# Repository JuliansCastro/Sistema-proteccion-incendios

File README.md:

# Sistema de Protección contra Incendios con LoRa y Raspberry Pi Pico

## Resumen

Este proyecto desarrolla un sistema integral de monitoreo y protección contra incendios forestales utilizando tecnología IoT. El sistema emplea sensores distribuidos que se comunican mediante protocolo LoRa para detectar condiciones ambientales críticas (temperatura, humedad y presencia de llamas) y transmitir los datos a una estación central basada en Raspberry Pi Pico W que proporciona interfaz web para visualización en tiempo real.

## Características Principales

- **Monitoreo Distribuido**: Red de sensores inalámbricos con comunicación LoRa de largo alcance
- **Detección Multiparamétrica**: Sensores de temperatura (DHT11), humedad relativa y detector PIR para llamas
- **Comunicación Robusta**: Protocolo LoRa a 433MHz con alcance de varios kilómetros
- **Interfaz Web**: Servidor HTTP integrado en Raspberry Pi Pico W para visualización remota
- **Display Local**: Pantalla LCD I2C para monitoreo local de datos
- **Alertas en Tiempo Real**: Detección automática de condiciones de riesgo de incendio
- **Arquitectura Modular**: Diseño escalable para múltiples nodos sensores
- **Bajo Consumo**: Optimizado para aplicaciones de campo con alimentación autónoma

## Arquitectura del Sistema

```text
┌─────────────────┐       LoRa 433MHz      ┌──────────────────────┐
│   Nodo Sensor   │ ◄────────────────────► │  Estación Central    │
│  (Tx - Pico)    │                        │  (Rx - Pico W)       │
├─────────────────┤                        ├──────────────────────┤
│ • DHT11         │                        │ • LoRa Receptor      │
│ • PIR Sensor    │                        │ • WiFi Server        │
│ • LoRa Tx       │                        │ • LCD Display        │
│ • Raspberry     │                        │ • Raspberry Pi       │
│   Pi Pico       │                        │   Pico W             │
└─────────────────┘                        └──────────────────────┘
                                                      │
                                                      │ WiFi
                                                      ▼
                                           ┌──────────────────────┐
                                           │   Cliente Web        │
                                           │ (Navegador/App)      │
                                           └──────────────────────┘
```

### Componentes del Sistema

1. **Nodo Transmisor (Tx)**:
   - Raspberry Pi Pico como microcontrolador principal
   - Sensor DHT11 para temperatura y humedad
   - Sensor PIR para detección de movimiento/llamas
   - Módulo LoRa para transmisión de datos
   - Encapsulado 3D impreso para protección ambiental

2. **Estación Receptora (Rx)**:
   - Raspberry Pi Pico W con conectividad WiFi
   - Módulo LoRa para recepción de datos
   - Display LCD I2C 16x2 para visualización local
   - Servidor web HTTP integrado
   - Procesamiento y almacenamiento temporal de datos

3. **Protocolo de Comunicación**:
   - LoRa a 433MHz para comunicación de largo alcance
   - Estructura de paquetes con ID de nodo, datos de sensores y verificación
   - Interfaz web HTTP para acceso remoto

## Tecnologías Utilizadas

### Hardware

- **Microcontroladores**:
  - Raspberry Pi Pico (RP2040)
  - Raspberry Pi Pico W (RP2040 + WiFi)
- **Sensores**:
  - DHT11 (Temperatura y Humedad)
  - PIR Sensor (Detección de movimiento/llamas)
- **Comunicación**:
  - Módulos LoRa SX1276/SX1278 (433MHz)
  - WiFi integrado (Pico W)
- **Display**: LCD I2C 16x2 con controlador PCF8574
- **PCB**: Diseño personalizado en KiCad
- **Encapsulado**: Carcasas 3D impresas en PLA/PETG

### Software

- **Lenguajes**: C++ (Arduino Framework)
- **Librerías**:
  - `LoRa.h` - Comunicación LoRa
  - `DHT.h` - Sensor de temperatura/humedad
  - `WiFi.h` - Conectividad inalámbrica
  - `LiquidCrystal_I2C.h` - Control de display
  - `TimeLib.h` - Manejo de tiempo
- **Protocolos**: HTTP, LoRa, I2C, SPI
- **IDE**: Arduino IDE con soporte para RP2040
- **Herramientas de Diseño**:
  - KiCad (Diseño de PCB)
  - Fusion 360 (Modelado 3D)

## Instalación y Configuración

### Requisitos de Hardware

- 2x Raspberry Pi Pico (1x estándar, 1x Pico W)
- 2x Módulos LoRa SX1276/SX1278
- 1x Sensor DHT11
- 1x Sensor PIR
- 1x Display LCD I2C 16x2
- Componentes electrónicos (resistencias, capacitores, conectores)
- PCBs personalizadas o protoboard
- Carcasas 3D impresas
- Fuentes de alimentación (baterías o adaptadores)

### Montaje y Conexiones

#### Nodo Transmisor (Pico)

```text
DHT11:
- VCC → 3.3V
- GND → GND  
- DATA → GPIO 28

PIR Sensor:
- VCC → 5V
- GND → GND
- OUT → GPIO 27

LoRa Module:
- VCC → 3.3V
- GND → GND
- NSS → GPIO 8
- RST → GPIO 9
- DIO0 → GPIO 7
- SCK → GPIO 18
- MISO → GPIO 16
- MOSI → GPIO 19
```

#### Estación Receptora (Pico W)

```text
LoRa Module:
- (Mismas conexiones que Tx)

LCD I2C:
- VCC → 3.3V
- GND → GND
- SDA → GPIO 0
- SCL → GPIO 1
```

### Instalación del Entorno de Software

1. **Configurar Arduino IDE**:

```bash
# Instalar Arduino IDE desde: https://www.arduino.cc/en/software

# Agregar soporte para RP2040:
# File → Preferences → Additional Board Manager URLs
# Agregar: https://github.com/earlephilhower/arduino-pico/releases/download/global/package_rp2040_index.json

# Tools → Board → Boards Manager
# Buscar "pico" e instalar "Raspberry Pi Pico/RP2040"
```

2. **Instalar Librerías Requeridas**:

```bash
# En Arduino IDE: Tools → Manage Libraries
# Instalar:
- DHT sensor library by Adafruit
- LoRa by Sandeep Mistry  
- LiquidCrystal I2C by Frank de Brabander
- Time by Michael Margolis
```

3. **Configurar Red WiFi**:

```cpp
// Editar en RPi_Pico_W_Lora_Rx.ino:
#define SSID "TU_RED_WIFI"
#define PASSWORD "TU_CONTRASEÑA"
```

4. **Cargar Firmware**:

```bash
# 1. Conectar Raspberry Pi Pico manteniendo presionado BOOTSEL
# 2. Seleccionar Board: "Raspberry Pi Pico" o "Raspberry Pi Pico W"
# 3. Cargar RPi_Pico_Lora_Tx.ino en el nodo transmisor
# 4. Cargar RPi_Pico_W_Lora_Rx.ino en la estación receptora
```

## Despliegue

### Ejecución Local

1. **Inicializar Sistema**:
   - Encender nodo transmisor (comenzará a enviar datos cada 20 segundos)
   - Encender estación receptora
   - Verificar conexión LoRa en monitor serial
   - Confirmar conexión WiFi y obtener IP local

2. **Acceso a Interface Web**:
   - Conectarse a la misma red WiFi que el Pico W
   - Abrir navegador en `http://[IP_DEL_PICO_W]`
   - La página se actualiza automáticamente cada 5 segundos

3. **Monitoreo Local**:
   - Visualizar datos en tiempo real en LCD
   - Revisar logs en monitor serial (115200 baud)

### Despliegue en Campo

1. **Preparación**:
   - Instalar nodos en ubicaciones estratégicas
   - Configurar alimentación autónoma (paneles solares/baterías)
   - Verificar cobertura LoRa entre nodos

2. **Red WiFi de Campo**:
   - Configurar hotspot móvil o router portable
   - Ajustar configuración WiFi en código según disponibilidad

## Casos de Uso

### Monitoreo Forestal

```text
Escenario: Bosque de 10 km²
- 5 nodos transmisores distribuidos estratégicamente
- 1 estación central con conectividad satelital/celular
- Alertas automáticas cuando temperatura > 35°C y humedad < 30%
- Detección temprana de focos de incendio mediante sensores PIR
```

### Instalaciones Industriales

```text
Escenario: Almacén de materiales inflamables
- Nodos en cada sector crítico
- Integración con sistemas de extinción automática
- Dashboard web para personal de seguridad
- Registro histórico de condiciones ambientales
```

### Agricultura de Precisión

```text
Escenario: Invernaderos automatizados
- Monitoreo continuo de microclima
- Optimización de sistemas de riego
- Prevención de condiciones de estrés térmico
- Alertas de condiciones anómalas
```

## Estructura del Proyecto

```text
Sistema-proteccion-incendios/
├── README.md
├── Carcasa - Fusion360/           # Modelos 3D de encapsulados
│   ├── 3D/                        # Archivos STL para impresión
│   └── Fusion360/                 # Archivos fuente F3D
├── Diseño electrónico - PCB KiCad/ # Diseños de circuitos impresos
│   ├── sys_incendios_rx/          # PCB para receptor
│   ├── sys_incendios_Tx/          # PCB para transmisor
│   └── Fab_PCB_diseno/            # Archivos Gerber para fabricación
├── Software microcontroladores/    # Código fuente
│   ├── RPi_Pico_Lora_Tx/         # Firmware nodo transmisor
│   └── RPi_Pico_W_Lora_Rx/       # Firmware estación receptora
├── Docs/                          # Documentación técnica
│   ├── BOOM Materials.xlsx        # Lista de materiales
│   └── Datasheets/                # Hojas de datos de componentes
└── imgs/                          # Imágenes del proyecto
```

## Desarrollo Futuro

- [ ] Integración con bases de datos (SQLite/MySQL)
- [ ] API REST para integración con terceros
- [ ] Aplicación móvil nativa
- [ ] Protocolo MQTT para IoT
- [ ] Integración con servicios en la nube (AWS IoT, Azure IoT)
- [ ] Algoritmos de machine learning para predicción
- [ ] Soporte para más tipos de sensores
- [ ] Mesh networking con múltiples receptores

## Contribuciones

Las contribuciones son bienvenidas. Para cambios importantes:

1. Fork el proyecto
2. Crear una rama para tu feature (`git checkout -b feature/AmazingFeature`)
3. Commit tus cambios (`git commit -m 'Add some AmazingFeature'`)
4. Push a la rama (`git push origin feature/AmazingFeature`)
5. Abrir un Pull Request

## Licencia

Este proyecto está licenciado bajo la Licencia MIT - ver el archivo [LICENSE](LICENSE) para detalles.

## Créditos y Autores

**Equipo de Desarrollo:**

- **Julian A. Castro** - *Líder del proyecto* - [juacastropa@unal.edu.co](mailto:juacastropa@unal.edu.co)
- **Daniela V. Amaya** - *Desarrollo de hardware*
- **Sebastian A. Moreno** - *Desarrollo de software*
- **Javier L. Rodríguez** - *Diseño mecánico*

**Institución:** Universidad Nacional de Colombia  
**Materia:** Diseño de Sistemas Electrónicos  
**Año:** 2023

---

## Agradecimientos

- Comunidad Arduino y Raspberry Pi Foundation
- Desarrolladores de las librerías utilizadas
- Universidad Nacional de Colombia por el apoyo académico

---

*Para soporte técnico o consultas, contactar al equipo de desarrollo a través de los emails proporcionados.*

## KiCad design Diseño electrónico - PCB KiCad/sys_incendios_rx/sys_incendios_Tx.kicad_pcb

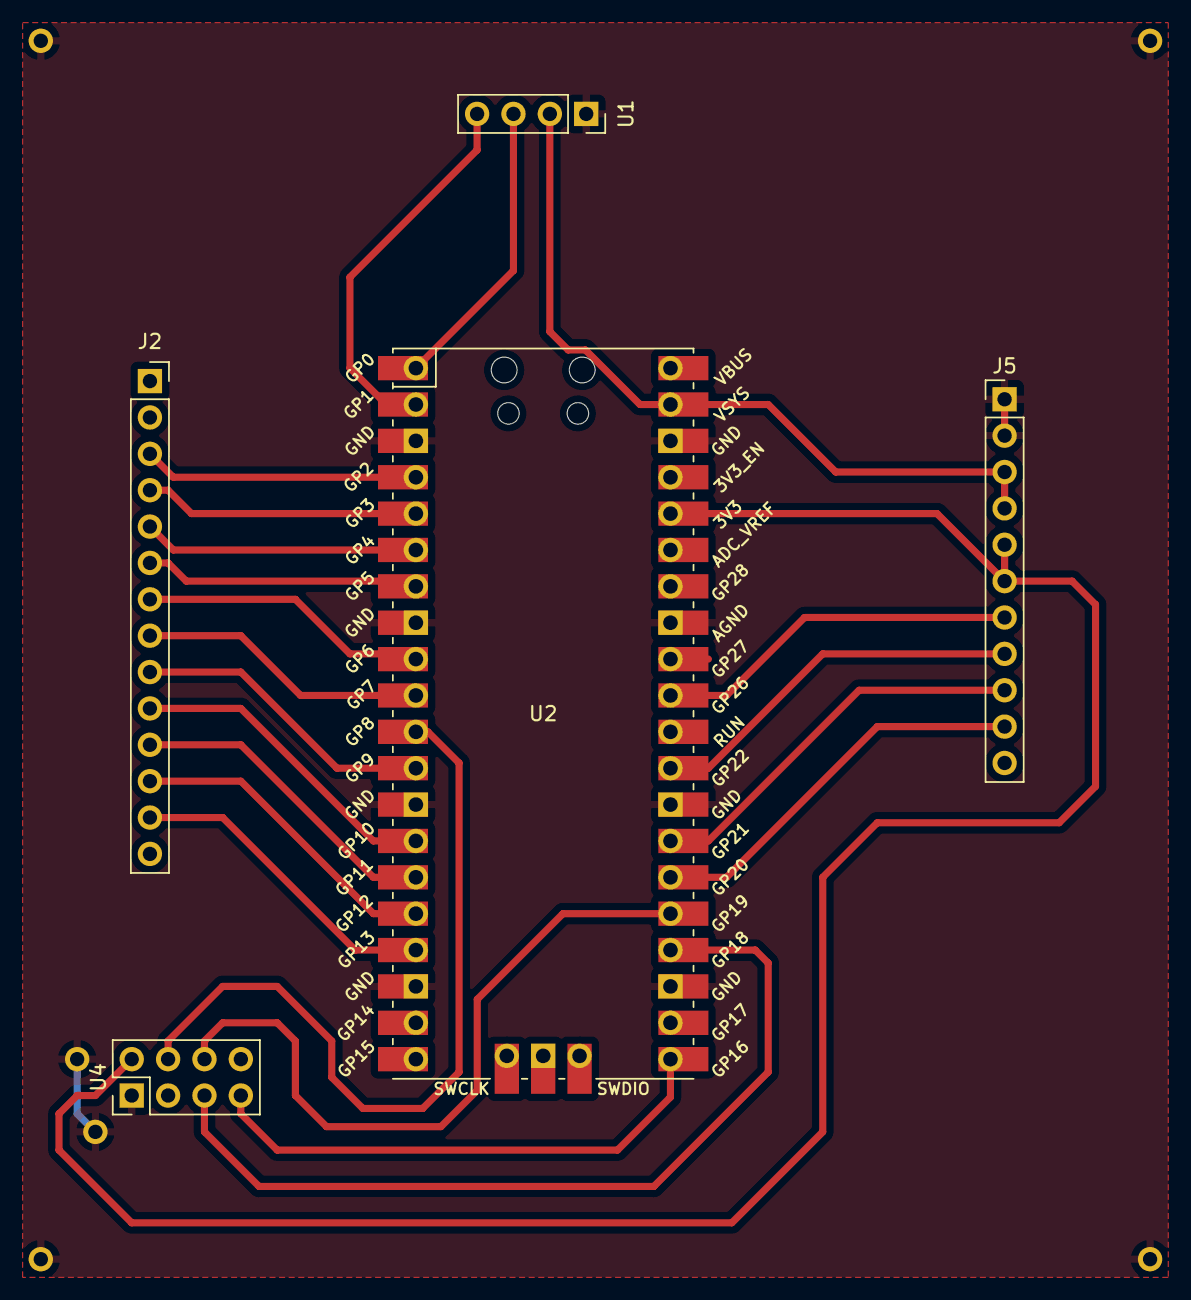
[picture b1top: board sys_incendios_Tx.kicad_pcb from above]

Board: 2 copper layers, 5 parts (0 on the bottom side), 24 nets.

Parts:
J2: Conn_01x15; PinSocket_1x14_P2.54mm_Vertical
J5: Conn_01x11; PinHeader_1x11_P2.54mm_Vertical
U1: LCD-DRIVER-I2C; Conn_LCD_Driver_16X2_module
U2: Pico; RPi_Pico_SMD_TH
U4: RA-02_LORA_mod_V4.0; PinHeader_2x04_P2.54mm_Vertical

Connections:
/3.3V: J5.5, J5.6, U2.36 (3V3), U4.2 (3.3V)
/GPIO2: J2.3, U2.4 (GPIO2)
/GPIO3: J2.4, U2.5 (GPIO3)
/GPIO4: J2.5, U2.6 (GPIO4)
/GPIO5: J2.6, U2.7 (GPIO5)
/GPIO6: J2.7, U2.9 (GPIO6)
/GPIO7: J2.8, U2.10 (GPIO7)
/GPIO9: J2.9, U2.12 (GPIO9)
/GPIO10: J2.10, U2.14 (GPIO10)
/GPIO11: J2.11, U2.15 (GPIO11)
/GPIO12: J2.12, U2.16 (GPIO12)
/GPIO13: J2.13, U2.17 (GPIO13)
/GPIO20: J5.10, U2.26 (GPIO20)
/GPIO21: J5.9, U2.27 (GPIO21)
/GPIO22: J5.8, U2.29 (GPIO22)
/GPIO26: J5.7, U2.31 (GPIO26_ADC0)
/MISO: U2.21 (GPIO16), U4.7 (MISO)
/MOSI: U2.25 (GPIO19), U4.6 (MOSI)
/NSS: U2.11 (GPIO8), U4.4 (NSS)
/SCK: U2.24 (GPIO18), U4.5 (SCK)
/SCL: U1.4 (SCL), U2.2 (GPIO1)
/SDA: U1.3 (SDA), U2.1 (GPIO0)
/vcc: J5.3, J5.4, U1.2 (VCC), U2.39 (VSYS)
GND: J5.1, J5.2, U1.1 (GND), U2.3 (GND), U2.8 (GND), U2.13 (GND), U2.18 (GND), U2.23 (GND), U2.28 (GND), U2.33 (AGND), U2.38 (GND), U4.1 (GND)

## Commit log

2023-11-02 Init commit
